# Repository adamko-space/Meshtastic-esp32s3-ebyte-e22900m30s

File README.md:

# ESP32s3 - devkit c1 n16r8 clone with CDEBYTE E22-900M30S - Variant for Meshtastic
I'm presenting my meshtastic node variant using a Chinese clone of the Esp32s3n61r8 devkit c1 board with 16MB flash, 8MB PSRAM, and the E22-900M30S module. After analyzing the free ESP pins, the connection is correct. The connection is described in the variant.h file.

E22900M30S requires

```bash
#define TX_GAIN_LORA 7 // gain module e22
#define SX126X_MAX_POWER 22 // max power + gain = max radio power - EU 27db
```
this is what the configure.h documentation says
```bash
// Gain for common modules with transmit PAs
#ifdef EBYTE_E22_900M30S
// 10dB PA gain and 30dB rated output; based on measurements from
// https://github.com/S5NC/EBYTE_ESP32-S3/blob/main/E22-900M30S%20power%20output%20testing.txt
#define TX_GAIN_LORA 7
#define SX126X_MAX_POWER 22
#endif
```

## 1. File info
- esp32-s3-devkit-e22/variant.h - define connection and setup configure
- esp32-s3-devkit-e22/platformio.ini - platformio config file
- esp32-s3-devkit-e22/pins_arduino.h - required config file for arduino/esp platforms
- boards/esp32-s3-devkit-e22.json - board devkit c1 clone configuration
- partion.csv - partition file for 16MB flash - put in header folder

## 2. Install and assembly
- Add files from this repository, keeping their proper locations to Meshtastic firmware
- compile the selected env and upload to your board
- connect the radio module as defined in the **variant.h** file
- **Make sure everything is in order so as not to damage the radio.**
- run node and test your network :)

## 3. Power
Standard consumption is approximately 110mA, with an average of 350-450mW at 27dBm during transmission.

- ADD a 100nF capacitor between the +5V power supply for the radio module and GND, and a 2000uF electrolytic capacitor to maintain power.

## 4. Troubleshooting
I'm on the 2.7.9-10 alpha software package.

-https ssl cert error during connect from client.meshtatistc.org

Apart from these issues, everything seems to be working fine.

## 5. Links

 - [Official Meshtastic webiste](meshtastic.org)
 - [Meshtastic Github](https://github.com/meshtastic)
 - [EByte Site E22900M30S](https://www.cdebyte.com/products/E22-900M30S/3)
 - [space.LAB](https://adamko.space/spacelab/)
 - If you like my work [donate my LAB -buycoffee.to](https://buycoffee.to/lab.adamko.space)

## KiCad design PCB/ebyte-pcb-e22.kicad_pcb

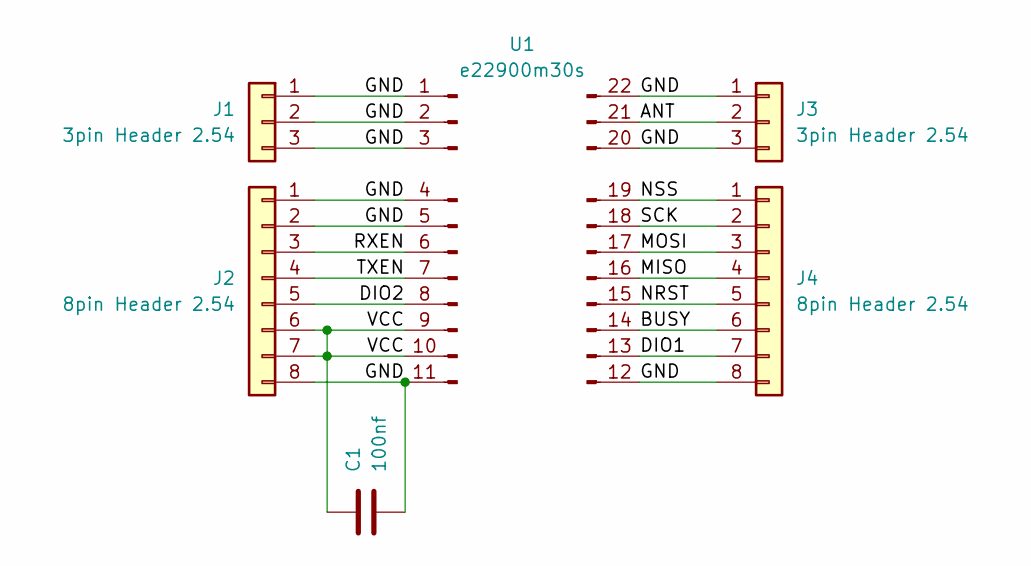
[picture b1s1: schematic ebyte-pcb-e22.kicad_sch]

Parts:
C1: 100nf; C_1206_3216Metric
J1, J3: 3pin Header 2.54; PinHeader_1x03_P2.54mm_Vertical
J2, J4: 8pin Header 2.54; PinHeader_1x08_P2.54mm_Vertical
U1: e22900m30s; PE22(400M30S)

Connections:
/ANT: J3.2, U1.21 (ANT)
/BUSY: J4.6, U1.14 (BUSY)
/DIO1: J4.7, U1.13 (DIO1)
/DIO2: J2.5, U1.8 (DIO2)
/GND: C1.2, J1.1, J1.2, J1.3, J2.1, J2.2, J2.8, J3.1, J3.3, J4.8, U1.1 (GND), U1.2 (GND), U1.3 (GND), U1.4 (GND), U1.5 (GND), U1.11 (GND), U1.12 (GND), U1.20 (GND), U1.22 (GND)
/MISO: J4.4, U1.16 (MISO)
/MOSI: J4.3, U1.17 (MOSI)
/NRST: J4.5, U1.15 (NRST)
/NSS: J4.1, U1.19 (NSS)
/RXEN: J2.3, U1.6 (RXEN)
/SCK: J4.2, U1.18 (SCK)
/TXEN: J2.4, U1.7 (TXEN)
/VCC: C1.1, J2.6, J2.7, U1.9 (VCC), U1.10 (VCC)

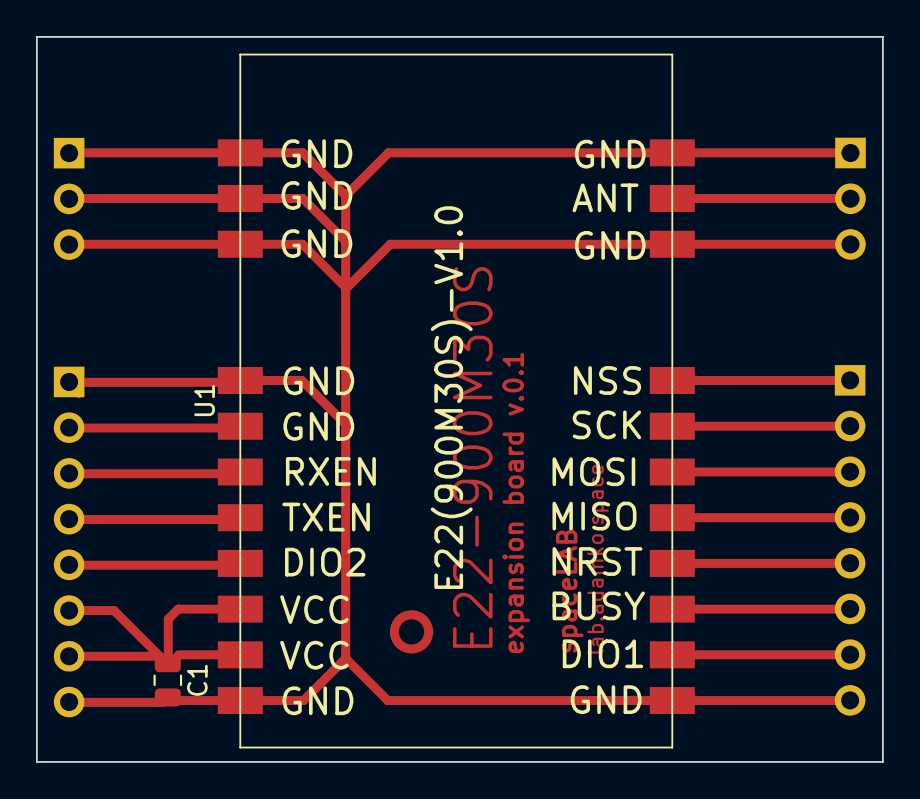
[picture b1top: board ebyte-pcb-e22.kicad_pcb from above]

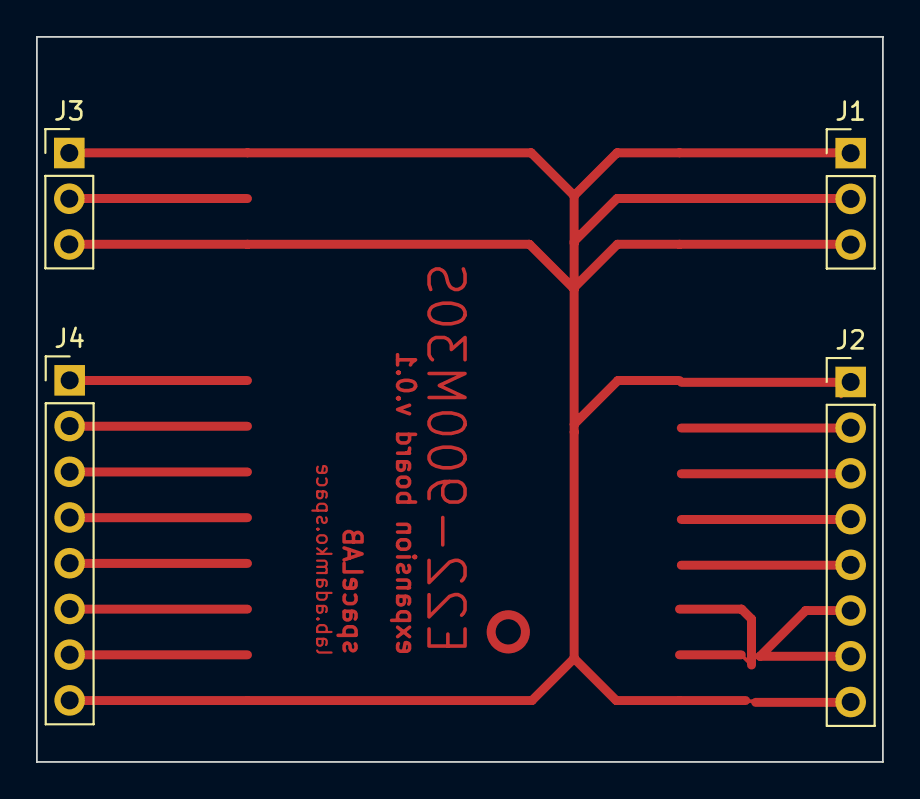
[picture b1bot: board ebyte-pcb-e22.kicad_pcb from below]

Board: 2 copper layers, 47.0 x 40.3 mm, 6 parts (4 on the bottom side), 13 nets.

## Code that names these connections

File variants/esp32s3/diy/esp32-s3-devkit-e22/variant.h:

#define HAS_LORA 1
#define USE_SX1262 1

#define TX_GAIN_LORA 7 // gain module e22
#define SX126X_MAX_POWER 22 // max power + gain = max radio power - EU 27db
#define SX126X_DIO3_TCXO_VOLTAGE 1.8 // required with documentation

#define SX126X_CS 14    // EBYTE module's NSS pin // FIXME: rename to SX126X_SS
#define SX126X_SCK 21   // EBYTE module's SCK pin
#define SX126X_MOSI 38 // EBYTE module's MOSI pin
#define SX126X_MISO 39 // EBYTE module's MISO pin  

#define SX126X_RESET 40 // EBYTE module's NRST pin
#define SX126X_BUSY 41 // EBYTE module's BUSY pin
#define SX126X_DIO1 42 // EBYTE module's DIO1 pin

#define SX126X_TXEN 9 // Schematic connects EBYTE module's TXEN pin to MCU
#define SX126X_RXEN 10 // Schematic connects EBYTE module's RXEN pin to MCU

#define LORA_CS SX126X_CS     // Compatibility with variant file configuration structure
#define LORA_SCK SX126X_SCK   // Compatibility with variant file configuration structure
#define LORA_MOSI SX126X_MOSI // Compatibility with variant file configuration structure
#define LORA_MISO SX126X_MISO // Compatibility with variant file configuration structure
#define LORA_DIO1 SX126X_DIO1 // Compatibility with variant file configuration structure


#define HAS_SCREEN 0 

#define BOARD_HAS_PSRAM


#define I2C_SCL 9
#define I2C_SDA 8

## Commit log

2025-09-29 v0.1
2025-09-29 0.1
    + pcb file
2025-09-30 fix pin v.0.1
